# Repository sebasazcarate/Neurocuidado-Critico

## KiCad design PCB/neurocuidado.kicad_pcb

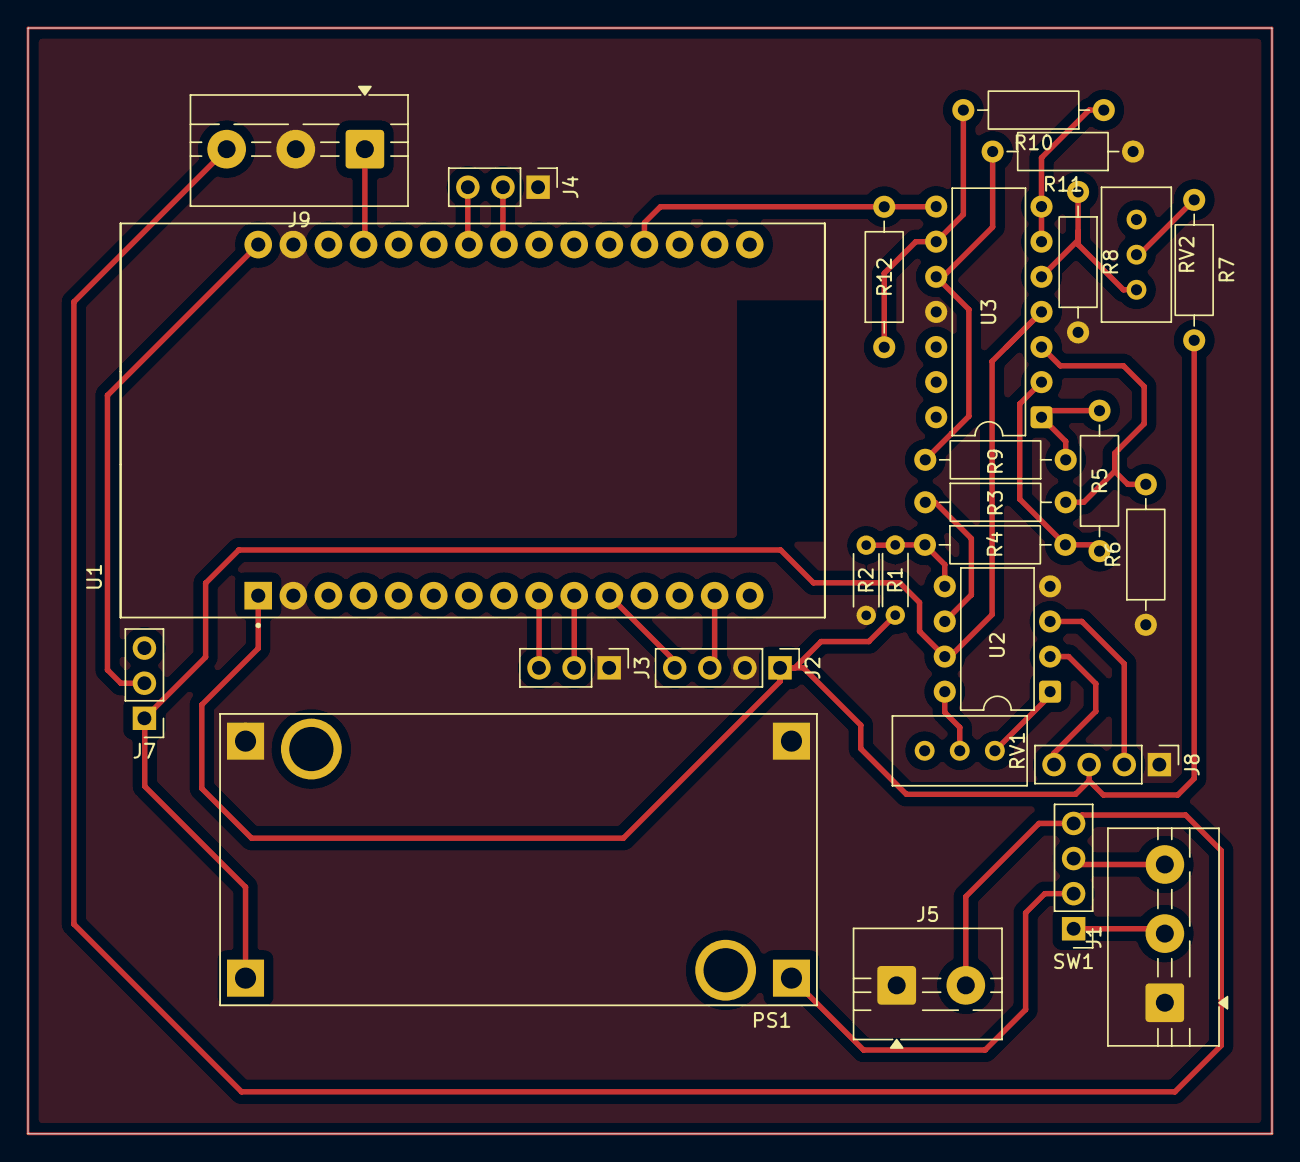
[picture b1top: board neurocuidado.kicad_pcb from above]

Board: 2 copper layers, 90.0 x 80.0 mm, 27 parts (0 on the bottom side), 30 nets.

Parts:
J1, J9: Screw_Terminal_01x03; TerminalBlock_MaiXu_MX126-5.0-03P_1x03_P5.00mm
J2, J8: Conn_01x04; PinHeader_1x04_P2.54mm_Vertical
J3, J4, J7: Conn_01x03; PinHeader_1x03_P2.54mm_Vertical
J5: Screw_Terminal_01x02; TerminalBlock_MaiXu_MX126-5.0-02P_1x02_P5.00mm
PS1: MC00100; CONV_MC00100
R1, R2: R; R_Axial_DIN0204_L3.6mm_D1.6mm_P5.08mm_Horizontal
R3, R4, R5, R6, R7, R8, R9, R10, R11, R12: R; R_Axial_DIN0207_L6.3mm_D2.5mm_P10.16mm_Horizontal
RV1, RV2: R_Potentiometer_Trim_US; Potentiometer_Bourns_3296W_Vertical
SW1: SW_DPST; PinHeader_1x04_P2.54mm_Vertical
U1: ESP32-DEVKIT-V1; MODULE_ESP32_DEVKIT_V1
U2: AD620; DIP-8_W7.62mm
U3: LM324A; DIP-14_W7.62mm

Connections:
+3V3: J2.1, J8.3, R1.1, R7.2, U1.1 (3V3)
+5V: J7.1, PS1.OUT+, U2.7 (Vs+), U3.4 (V+)
+5VA: J1.2, SW1.1
+5VD: J7.2, U1.30 (VIN)
+7.5V: PS1.IN+, SW1.2
+12V: J5.2, J9.3, SW1.4
+12VA: J1.3, SW1.3
DIR: J4.3, U1.24 (D26)
GND: J1.1, J2.2, J3.1, J4.1, J5.1, J8.1, J9.2, PS1.IN-, PS1.OUT-, R2.2, R6.1, R8.2, R11.1, U1.2 (GND), U1.29 (GND), U2.4 (Vs-), U3.11 (V-)
unnamed: R3.1, U2.6
unnamed: R5.2, R9.1, U3.1
unnamed: R7.1, RV2.2
unnamed: RV1.1, U2.1 (Rg)
unnamed: RV1.2, U2.8 (Rg)
unnamed: R1.2, R2.1, R4.1, U2.5 (Ref)
unnamed: R3.2, R6.2, U3.3 (+)
unnamed: R4.2, R5.1, U3.2 (-)
unnamed: R8.1, RV2.1, U3.5 (+)
unnamed: R10.1, U3.6 (-), U3.7
unnamed: R9.2, R11.2, U3.10 (+)
unnamed: R10.2, R12.1, U3.9 (-)
PRESSURE: R12.2, U1.19 (D34), U3.8
PUL: J4.2, U1.23 (D25)
Rele: J9.1, U1.27 (D12)
SCL: J2.3, U1.14 (D22)
SDA: J2.4, U1.11 (D21)
SWL: J3.2, U1.10 (D19)
SWR: J3.3, U1.9 (D18)
VOUT+: J8.2, U2.3 (+)
VOUT-: J8.4, U2.2 (-)
